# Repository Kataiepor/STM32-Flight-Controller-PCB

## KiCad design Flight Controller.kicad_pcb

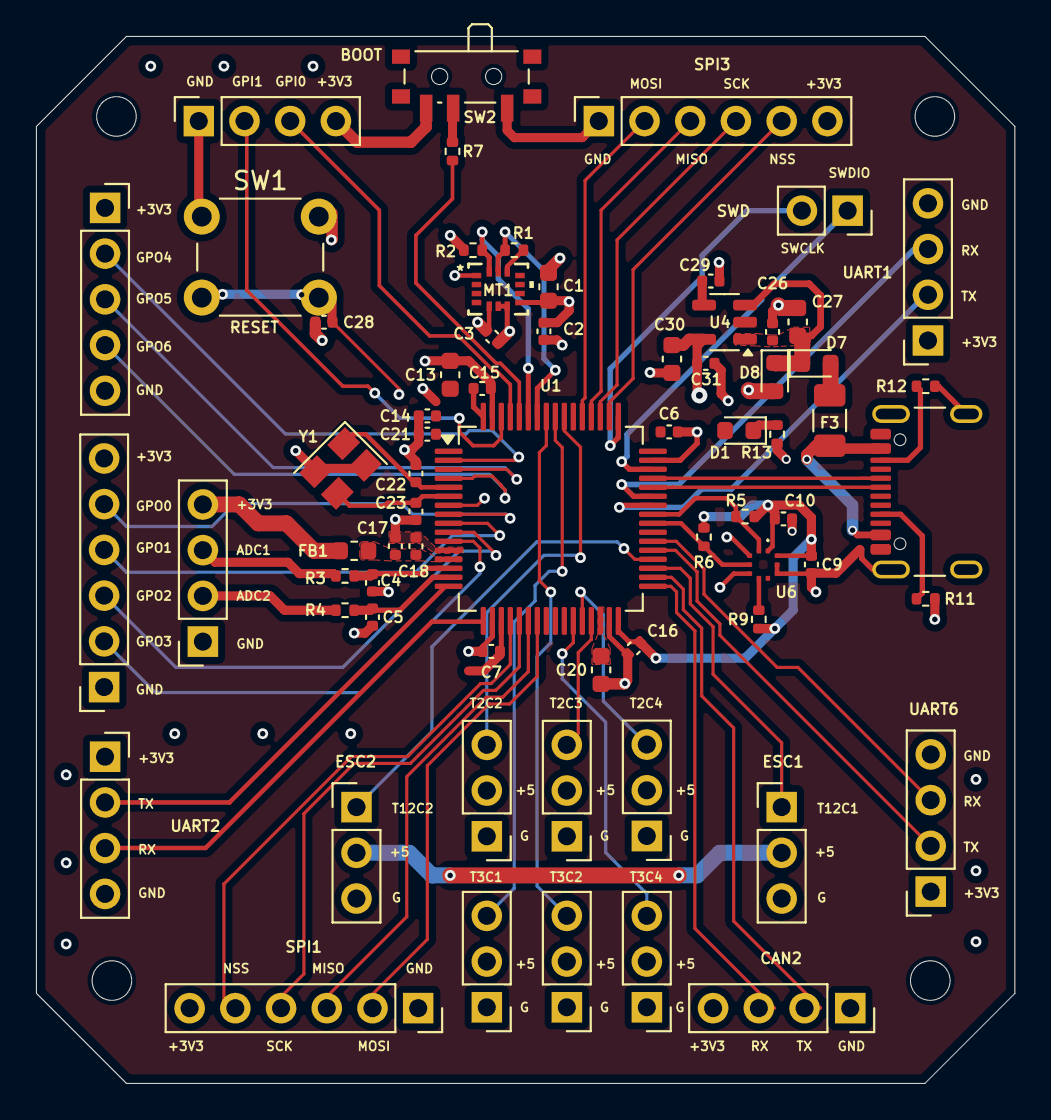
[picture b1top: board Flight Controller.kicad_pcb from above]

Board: 2 copper layers, 54.4 x 58.2 mm, 72 parts (0 on the bottom side), 10 nets.

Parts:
C1, C27, C30: 2u2; C_0603_1608Metric
C2, C4, C5, C6, C7, C9, C10, C14, C15, C16, C17, C21, C26, C28, C31: 100n; C_0402_1005Metric
C3, C29: 10n; C_0402_1005Metric
C13: 10u; C_0603_1608Metric
C18: 1u; C_0402_1005Metric
C20: 4u7; C_0603_1608Metric
C22, C23: 35p; C_0402_1005Metric
D1: GRN; LED_0603_1608Metric
D7, D8: B120-E3; D_0603_1608Metric
F3: Fuse; Fuse_1206_3216Metric
FB1: 600R FerriteBead; L_0603_1608Metric
H1, H2, H3, H4: MountingHole; MountingHole_2.2mm_M2
J1: SPI3; PinSocket_1x06_P2.54mm_Vertical
J2: GPIOOUT_1; PinSocket_1x06_P2.54mm_Vertical
J3: USART_1; PinSocket_1x04_P2.54mm_Vertical
J4: GPIOIN; PinSocket_1x04_P2.54mm_Vertical
J5: ADC; PinSocket_1x04_P2.54mm_Vertical
J6: USART_2; PinSocket_1x04_P2.54mm_Vertical
J7: USART_6; PinSocket_1x04_P2.54mm_Vertical
J8: SERVO_1; PinHeader_1x03_P2.54mm_Vertical
J9: SERVO_2; PinHeader_1x03_P2.54mm_Vertical
J10: GPIOOUT_2; PinSocket_1x05_P2.54mm_Vertical
J11: SWD; PinSocket_1x02_P2.54mm_Vertical
J12: SERVO_5; PinHeader_1x03_P2.54mm_Vertical
J13: SERVO_4; PinHeader_1x03_P2.54mm_Vertical
J14: SERVO_6; PinHeader_1x03_P2.54mm_Vertical
J15: SERVO_3; PinHeader_1x03_P2.54mm_Vertical
J17: SPI1; PinSocket_1x06_P2.54mm_Vertical
J18: CAN2; PinSocket_1x04_P2.54mm_Vertical
J21: B1_IN; PinHeader_1x03_P2.54mm_Vertical
J22: B2_IN; PinHeader_1x03_P2.54mm_Vertical
J23: USB_IN; USB_C_Receptacle_GCT_USB4105-xx-A_16P_TopMnt_Horizontal
MT1: ICM-42670-P; LGA14_2.5X3X0.76_IVS
R1, R2: 10K; R_0402_1005Metric
R3, R4: 100; R_0402_1005Metric
R5, R6, R7, R11, R12, R13: 4K7; R_0402_1005Metric
R9: 100K; R_0402_1005Metric
SW1: SW_Push; SW_PUSH_6mm_H5mm
SW2: SW_SPDT; SW_SPDT_PCM12
U1: STM32F446RETx; LQFP-64_10x10mm_P0.5mm
U4: 3V3; SOT-23-5
U6: BMP390
Y1: Crystal_GND24; Crystal_SMD_3225-4Pin_3.2x2.5mm

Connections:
GND: C1.2, C2.2, C3.2, C4.1, C5.1, C6.2, C7.2, C9.2, C10.2, C13.2, C14.2, C15.2, C16.2, C17.2, C18.2, C20.2, C21.1, C22.2, C23.2, C26.2, C27.2, C28.2, C29.2, C30.2, C31.2, J1.1, J2.1, J3.4, J4.1, J5.1, J6.4, J7.4, J8.1, J9.1, J10.5, J12.1, J13.1, J14.1, J15.1, J17.1, J18.1, J21.3, J22.3, J23.A1 (GND), J23.A12 (GND), J23.B1 (GND), J23.B12 (GND), J23.S1 (SHIELD), MT1.1 (AP_SDO/AP_AD0), MT1.6 (GND), MT1.7 (FSYNC), R11.2, R12.2, R13.2, SW2.1 (A), U1.12 (VSSA), U1.18 (VSS), U1.31 (VSS), U1.47 (VSS), U1.63 (VSS), U4.2 (GND), U6.3 (VSS), U6.5 (SDO), U6.8 (VSS), U6.9 (VSS), Y1.2, Y1.4
I2C1_SCL: MT1.13 (AP_SCL/AP_SCLK), R1.2, U1.58 (PB6)
I2C1_SDA: MT1.14 (AP_SDA/AP_SDIO/AP_SDI), R2.2, U1.59 (PB7)
I2C3_SCL: R5.2, U1.41 (PA8), U6.2 (SCK)
I2C3_SDA: R6.1, U1.40 (PC9), U6.4 (SDI)
NRST: C28.1, U1.7 (NRST)
TIM12_CH1: J21.1, U1.35 (PB14)
TIM12_CH2: J22.1, U1.36 (PB15)
USB-D+: J23.A6 (D+), J23.B6 (D+), U1.45 (PA12)
USB-D-: J23.A7 (D-), J23.B7 (D-), U1.44 (PA11)

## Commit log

2025-10-06 Rename Flight Controller.kicad_pcb to Flight_Controller.kicad_pcb
2025-10-06 Rename FCV Project 3D.glb to FCV_Project_3D.glb
2025-10-06 Rename Flight Controller 3D.glb to Flight_Controller_3D.glb
